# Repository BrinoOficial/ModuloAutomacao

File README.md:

# ModuloAutomacao
Um módulo com base no franzininho para uma automação residencial simples e de baixo custo. A ideia é utilizar um controle remoto IR qualquer para poder ligar e deligar uma tomada. Com isso é possivel controlar coisas como lâmpadas e ventiladores com o clicar de um botão de sua TV.

## Quer saber como montar o projeto? Confira agora mesmo a [wiki](https://github.com/BrinoOficial/ModuloAutomacao/wiki)!

## Versão
Desenvolvido no Ubuntu 16.04 LTS 64Bits
* **Brino** - *3.0.1*
* **Arduino** - *2:1.0.5*
* **Eagle** - **
* **Fusion** - **

## Autores

* **Víctor Rodrigues Pacheco** - *Autor* - [granix3](https://github.com/granix3)
* **Gabriel Rodrigues Pacheco** - *Autor* - [GabrielRPacheco](https://github.com/gabrielRPacheco)
* **Mateus Berardo de Souza Terra** - *Autor* - [MatTerra](https://github.com/MatTerra)

Veja também a lista de [contributors](https://github.com/BrinoOficial/ModuloAutomacao/graphs/contributors).

## Licença

Este projeto está sob a licença do MIT - Veja em [LICENSE.md](LICENSE.md) arquivo para mais detalhes

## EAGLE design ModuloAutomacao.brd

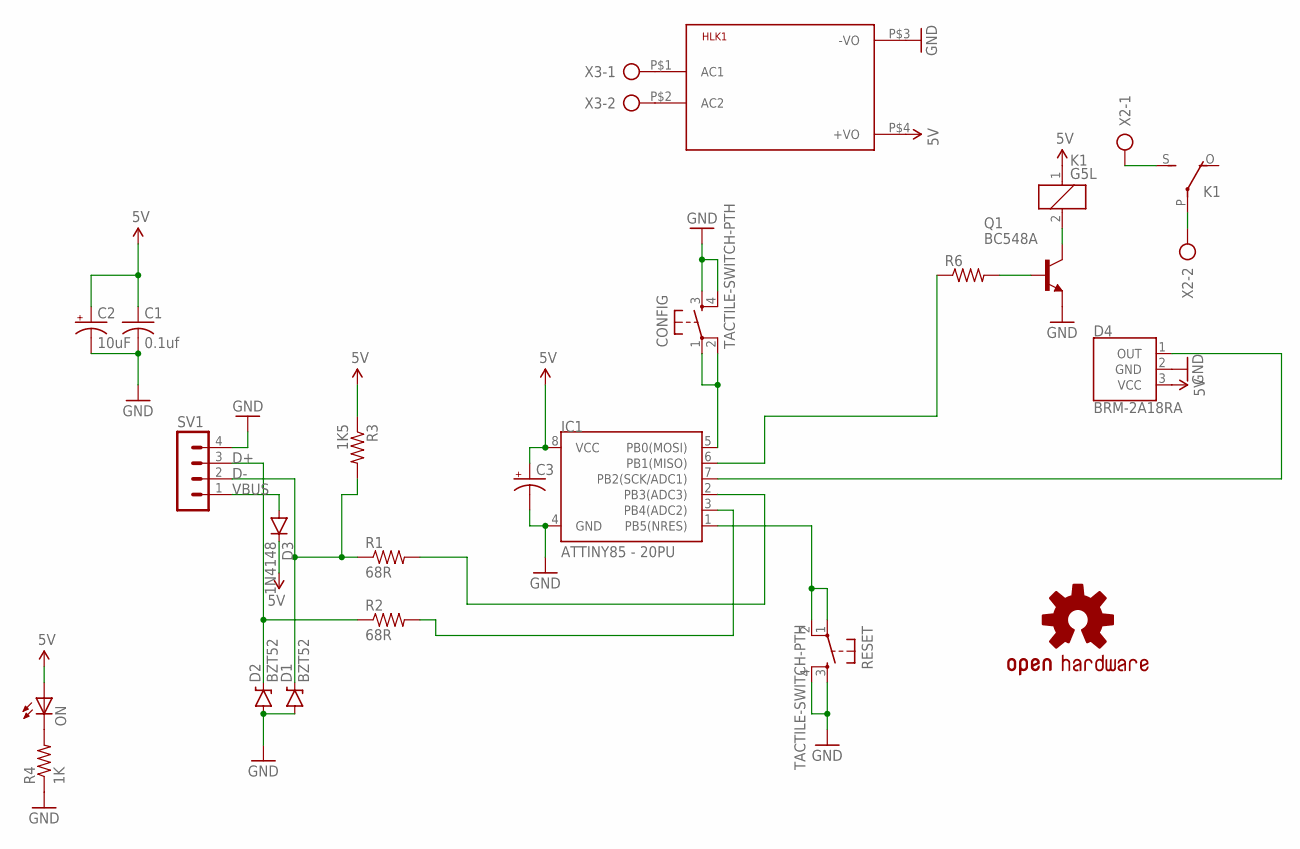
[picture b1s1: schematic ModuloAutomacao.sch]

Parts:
C1: 0.1uf; C025-025X050
C2: 10uF; E2,5-6E
C3: CPOL-USE1.8-4; E1,8-4
CONFIG: TACTILE-SWITCH-PTH; TAC-SWITCH-PTH
D1, D2: BZT52; DIODE-BZT52
D3: 1N4148; DIODE-1N4148
D4: BRM-2A18RA; BRM-2508
HLK1: HLK-PM013W; HLK-PM01
IC1: ATTINY85 - 20PU; DIP08
K1: G5L; G5LE
LOGO1: OSHW-LOGOM; OSHW-LOGO-M
ON: LED3MM
Q1: BC548A; TO92-EBC
R1, R2: 68R; AXIAL-0.4
R3: 1K5; AXIAL-0.4
R4: 1K; AXIAL-0.4
R6: R-US_0204/7; 0204/7
RESET: TACTILE-SWITCH-PTH; TAC-SWITCH-PTH
SV1: MA04-1
X2, X3: AK300/2

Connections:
5V: C1.1, C2.+, C3.+, D3.C, D4.3 (VCC), HLK1.P$4 (+VO), IC1.8 (VCC), K1.1, ON.A, R3.P$1 (1)
D+: D2.C, R2.P$1 (1), SV1.3
D-: D1.C, R1.P$1 (1), R3.P$2 (2), SV1.2
GND: C1.2, C2.-, C3.-, CONFIG.3, CONFIG.4, D1.A, D2.A, D4.2 (GND), HLK1.P$3 (-VO), IC1.4 (GND), Q1.E, R4.P$1 (1), RESET.3, RESET.4, SV1.4
unnamed: IC1.2 (PB3(ADC3)), R1.P$2 (2)
unnamed: IC1.6 (PB1(MISO)), R6.1
unnamed: CONFIG.1, CONFIG.2, IC1.5 (PB0(MOSI))
unnamed: D4.1 (OUT), IC1.7 (PB2(SCK/ADC1))
unnamed: IC1.3 (PB4(ADC2)), R2.P$2 (2)
unnamed: IC1.1 (PB5(NRES)), RESET.1, RESET.2
unnamed: K1.2, Q1.C
unnamed: Q1.B, R6.2
unnamed: HLK1.P$1 (AC1), X3.1
unnamed: HLK1.P$2 (AC2), X3.2
unnamed: K1.P, X2.2
unnamed: ON.K (C), R4.P$2 (2)
unnamed: K1.S, X2.1
VBUS: D3.A, SV1.1

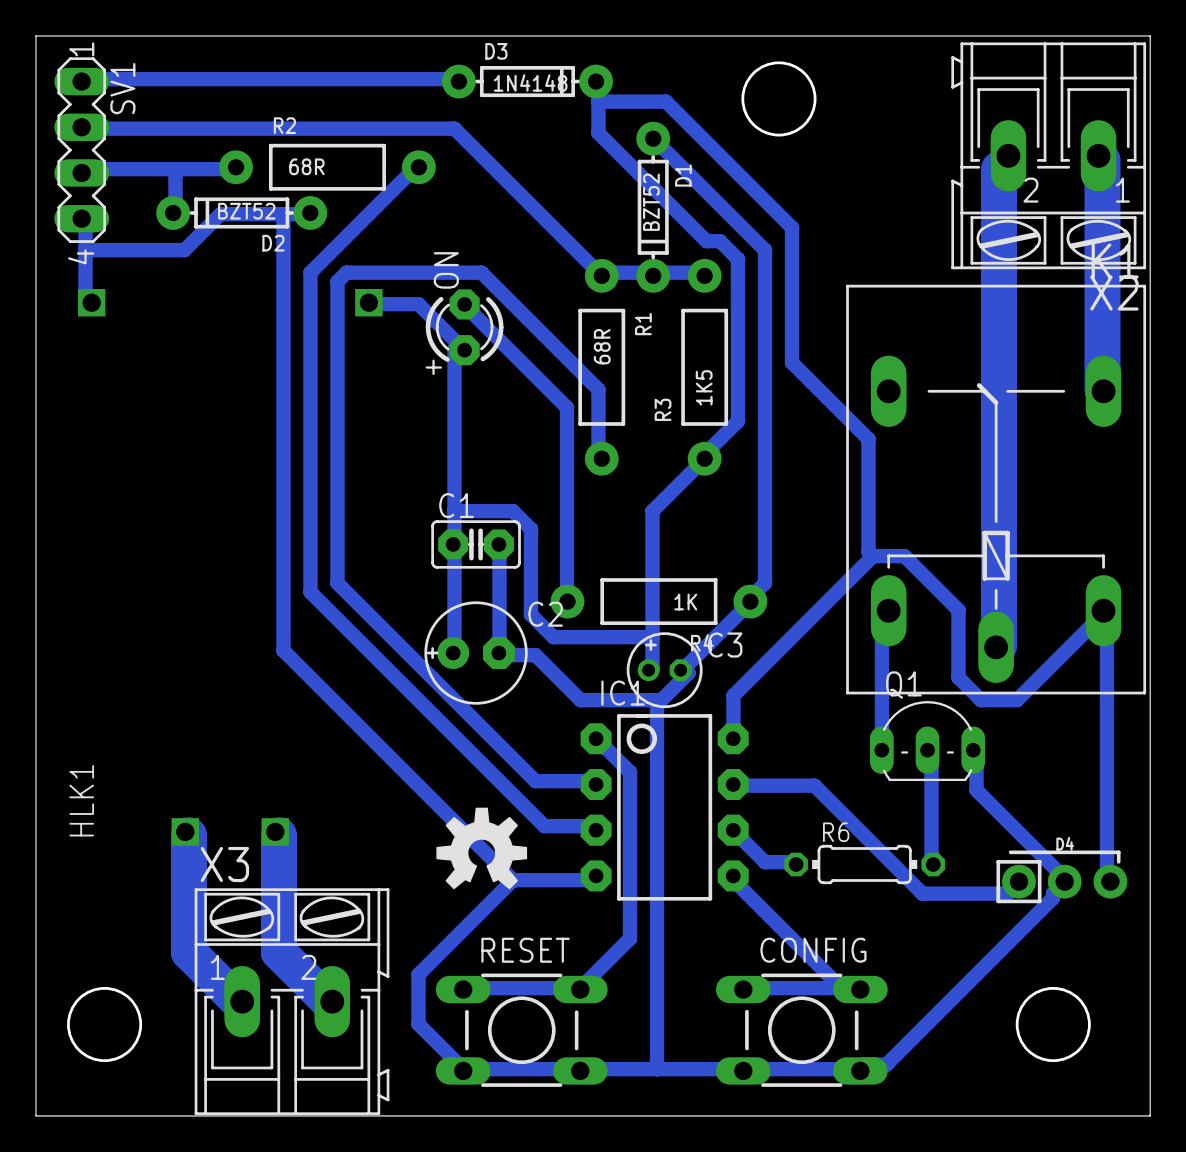
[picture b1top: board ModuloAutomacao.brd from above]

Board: 2 copper layers, 61.7 x 59.8 mm, 23 parts (0 on the bottom side), 18 nets.

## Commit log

2018-05-31 Case

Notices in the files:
parts and their libraries:
SparkFun-DiscreteSemi: Licensing: Creative Commons ShareAlike 4.0 International - https://creativecommons.org/licenses/by-sa/4.0
SparkFun: Licensing: CC v3.0 Share-Alike You are welcome to use this library for commercial purposes.
